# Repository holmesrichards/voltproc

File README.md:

# Voltage processor

This is a voltage processor module based on designs by ARP and MFOS.

There are two sum sections: One has four inputs, two with attenuators (normaled to -10 V and +10 V) and two with fixed unity gain; the other has two inputs, one with attenuator (normaled to +10 V) and one with fixed unity gain. Each sum has two outputs, normal and inverted.

There also is a lag processor section. Switches allow selection of slow or fast ranges and RC or linear ramping, and a knob adjusts the lag time.

The sum sections are derived from the ARP 2600 schematics. Differences:

* Obviously, this is a module, so there is no normal connection to keyboard CV; instead the second input of the first sum is normaled to +10 V.
* Added second inverting stages for normal plus inverted outputs.
* TL07x op amps in place of LM301.
* Added series output resistors.

The lag processor is based on a section of the MFOS Multi Function Module. Differences:

* Common input and output for both linear and RC circuits.
* Shorter minimum linear lag time.
* 1k series resistors on outputs.

## Current draw
20 mA +12 V, 20 mA -12 V

## Photos

## Documentation

* [Schematic](Docs/voltproc.pdf)
* PCB layout: [front](Docs/voltproc_layout_front.pdf), [back](Docs/voltproc_layout_back.pdf)
* [BOM](Docs/voltproc_bom.md)
* [Build notes](Docs/build.md)
* [Blog post](https://analogoutputblog.wordpress.com/2022/11/26/processing-voltages/)

## GitHub repository

* [https://github.com/holmesrichards/voltproc](https://github.com/holmesrichards/voltproc)

## Submodules

## Submodules

This repo uses submodules aoKicad and Kosmo_panel, which provide needed libaries for KiCad. To clone:

```
git clone git@github.com:holmesrichards/voltproc.git
git submodule init
git submodule update
```

Alternatively do

```
git clone --recurse-submodules git@github.com:holmesrichards/voltproc.git
```

Or if you download the repository as a zip file, you must also click on the "aoKicad" and "Kosmo\_panel" links on the GitHub page (they'll have "@ something" after them) and download them as separate zip files which you can unzip into this repo's aoKicad and Kosmo\_panel directories.

If desired, copy the files from aoKicad and Kosmo\_panel to wherever you prefer (your KiCad user library directory, for instance, if you have one). Then in KiCad, go into Edit Symbols and add symbol libraries 

```
aoKicad/ao_symbols
Kosmo_panel/Kosmo
```
and go into Edit Footprints and add footprint libraries 
```
aoKicad/ao_tht
Kosmo_panel/Kosmo_panel.
```

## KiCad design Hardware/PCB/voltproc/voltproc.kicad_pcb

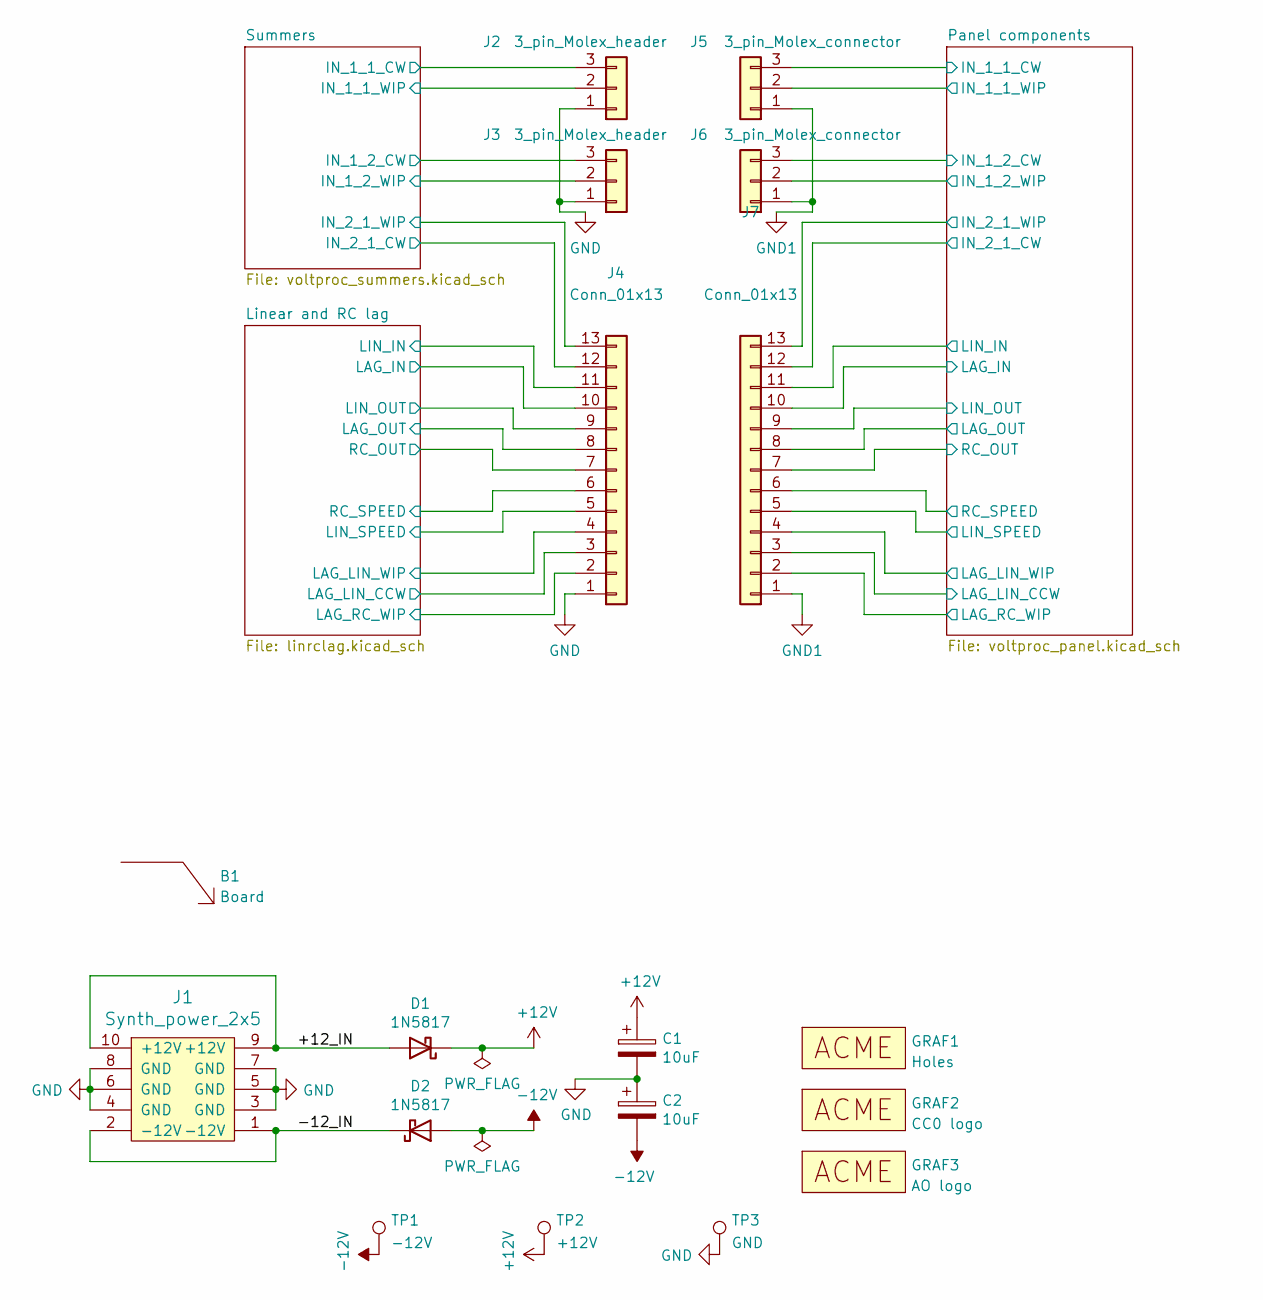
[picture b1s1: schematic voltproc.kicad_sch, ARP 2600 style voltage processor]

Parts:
B1: Board; Board_Marker
C1, C2: 10uF; CP_Radial_D6.3mm_P2.50mm
D1, D2: 1N5817; D_DO-41_SOD81_P10.16mm_Horizontal
GRAF1: Holes; voltproc_panel_holes
GRAF2: CC0 logo; CC0_logo
GRAF3: AO logo; analogoutput
J1: Synth_power_2x5; Power_Header
J2, J3: 3_pin_Molex_header; Molex_KK-254_AE-6410-03A_1x03_P2.54mm_Vertical
J4: Conn_01x13; PinHeader_1x13_P2.54mm_Vertical
J5, J6: 3_pin_Molex_connector; Molex_KK-254_AE-6410-03A_1x03_P2.54mm_Vertical
J7: Conn_01x13; PinSocket_1x13_P2.54mm_Vertical
TP1: -12V; TestPoint_THTPad_D1.5mm_Drill0.7mm
TP2: +12V; TestPoint_THTPad_D1.5mm_Drill0.7mm
TP3: GND; TestPoint_THTPad_D1.5mm_Drill0.7mm

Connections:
+12V: C1.1, D1.1 (K), TP2.1; also elsewhere on the board
-12V: C2.2, D2.2 (A), TP1.1; also elsewhere on the board
/+12_IN: D1.2 (A), J1.9 (+12V), J1.10 (+12V)
/-12_IN: D2.1 (K), J1.1 (-12V), J1.2 (-12V)
/Linear and RC lag/LAG_IN: J4.10; also elsewhere on the board
/Linear and RC lag/LAG_LIN_CCW: J4.3; also elsewhere on the board
/Linear and RC lag/LAG_LIN_WIP: J4.4; also elsewhere on the board
/Linear and RC lag/LAG_OUT: J4.8; also elsewhere on the board
/Linear and RC lag/LAG_RC_WIP: J4.2; also elsewhere on the board
/Linear and RC lag/LIN_IN: J4.11; also elsewhere on the board
/Linear and RC lag/LIN_OUT: J4.9; also elsewhere on the board
/Linear and RC lag/LIN_SPEED: J4.5; also elsewhere on the board
/Linear and RC lag/RC_OUT: J4.7; also elsewhere on the board
/Linear and RC lag/RC_SPEED: J4.6; also elsewhere on the board
/Panel components/IN_2_1_CW: J7.12; also elsewhere on the board
/Panel components/IN_2_1_WIP: J7.13; also elsewhere on the board
/Panel components/LAG_IN: J7.10; also elsewhere on the board
/Panel components/LAG_LIN_CCW: J7.3; also elsewhere on the board
/Panel components/LAG_LIN_WIP: J7.4; also elsewhere on the board
/Panel components/LAG_OUT: J7.8; also elsewhere on the board
/Panel components/LAG_RC_WIP: J7.2; also elsewhere on the board
/Panel components/LIN_IN: J7.11; also elsewhere on the board
/Panel components/LIN_OUT: J7.9; also elsewhere on the board
/Panel components/LIN_SPEED: J7.5; also elsewhere on the board
/Panel components/RC_OUT: J7.7; also elsewhere on the board
/Panel components/RC_SPEED: J7.6; also elsewhere on the board
/Summers/IN_1_1_CW: J2.3; also elsewhere on the board
/Summers/IN_1_1_WIP: J2.2; also elsewhere on the board
/Summers/IN_1_2_CW: J3.3; also elsewhere on the board
/Summers/IN_1_2_WIP: J3.2; also elsewhere on the board
/Summers/IN_2_1_CW: J4.12; also elsewhere on the board
/Summers/IN_2_1_WIP: J4.13; also elsewhere on the board
GND: C1.2, C2.1, J1.3 (GND), J1.4 (GND), J1.5 (GND), J1.6 (GND), J1.7 (GND), J1.8 (GND), J2.1, J3.1, J4.1, TP3.1; also elsewhere on the board
GND1: J5.1, J6.1, J7.1; also elsewhere on the board

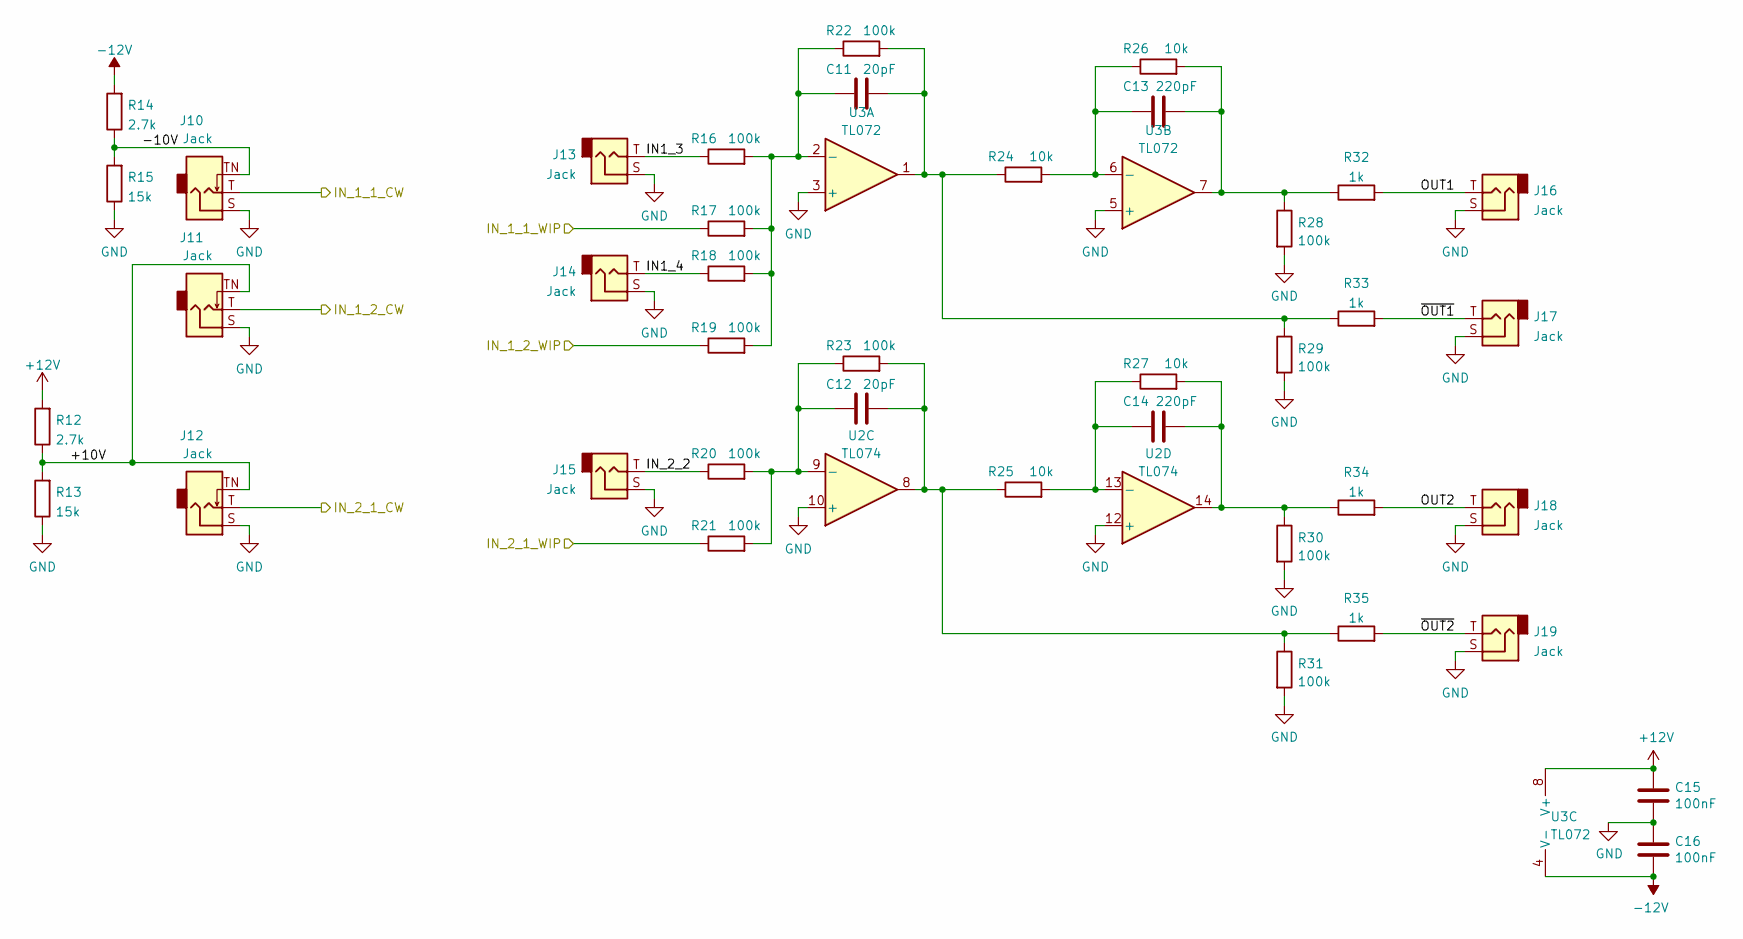
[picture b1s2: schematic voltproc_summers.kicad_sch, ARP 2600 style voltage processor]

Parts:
C11, C12: 20pF; C_Disc_D3.0mm_W1.6mm_P2.50mm
C13, C14: 220pF; C_Disc_D3.0mm_W1.6mm_P2.50mm
C15, C16: 100nF; C_Disc_D3.0mm_W1.6mm_P2.50mm
J10, J11, J12, J13, J14, J15, J16, J17, J18, J19: Jack; Jack_6.35mm_PJ_629HAN_slots
R12, R14: 2.7k; R_Axial_DIN0207_L6.3mm_D2.5mm_P10.16mm_Horizontal
R13, R15: 15k; R_Axial_DIN0207_L6.3mm_D2.5mm_P10.16mm_Horizontal
R16, R17, R18, R19, R20, R21, R22, R23, R28, R29, R30, R31: 100k; R_Axial_DIN0207_L6.3mm_D2.5mm_P10.16mm_Horizontal
R24, R25, R26, R27: 10k; R_Axial_DIN0207_L6.3mm_D2.5mm_P10.16mm_Horizontal
R32, R33, R34, R35: 1k; R_Axial_DIN0207_L6.3mm_D2.5mm_P10.16mm_Horizontal
U2: TL074; DIP-14_W7.62mm_Socket_LongPads
U3: TL072; DIP-8_W7.62mm_Socket_LongPads

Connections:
+12V: C15.1, R12.2, U3.8 (V+); also elsewhere on the board
-12V: C16.2, R14.2, U3.4 (V-); also elsewhere on the board
/Summers/+10V: J11.TN, J12.TN, R12.1, R13.2
/Summers/-10V: J10.TN, R14.1, R15.2
/Summers/IN1_3: J13.T, R16.1
/Summers/IN1_4: J14.T, R18.1
/Summers/IN_1_1_CW: J10.T; also elsewhere on the board
/Summers/IN_1_1_WIP: R17.1; also elsewhere on the board
/Summers/IN_1_2_CW: J11.T; also elsewhere on the board
/Summers/IN_1_2_WIP: R19.1; also elsewhere on the board
/Summers/IN_2_1_CW: J12.T; also elsewhere on the board
/Summers/IN_2_1_WIP: R21.1; also elsewhere on the board
/Summers/IN_2_2: J15.T, R20.1
/Summers/OUT1: J16.T, R32.2
/Summers/OUT2: J18.T, R34.2
/Summers/~OUT1: J17.T, R33.2
/Summers/~OUT2: J19.T, R35.2
GND: C15.2, C16.1, J10.S, J11.S, J12.S, J13.S, J14.S, J15.S, J16.S, J17.S, J18.S, J19.S, R13.1, R15.1, R28.2, R29.2, R30.2, R31.2, U2.10 (+), U2.12 (+), U3.3 (+), U3.5 (+); also elsewhere on the board
unnamed: C11.1, R16.2, R17.2, R18.2, R19.2, R22.1, U3.2 (-)
unnamed: C11.2, R22.2, R24.1, R29.1, R33.1, U3.1
unnamed: C12.1, R20.2, R21.2, R23.1, U2.9 (-)
unnamed: C12.2, R23.2, R25.1, R31.1, R35.1, U2.8
unnamed: C13.1, R24.2, R26.1, U3.6 (-)
unnamed: C13.2, R26.2, R28.1, R32.1, U3.7
unnamed: C14.1, R25.2, R27.1, U2.13 (-)
unnamed: C14.2, R27.2, R30.1, R34.1, U2.14

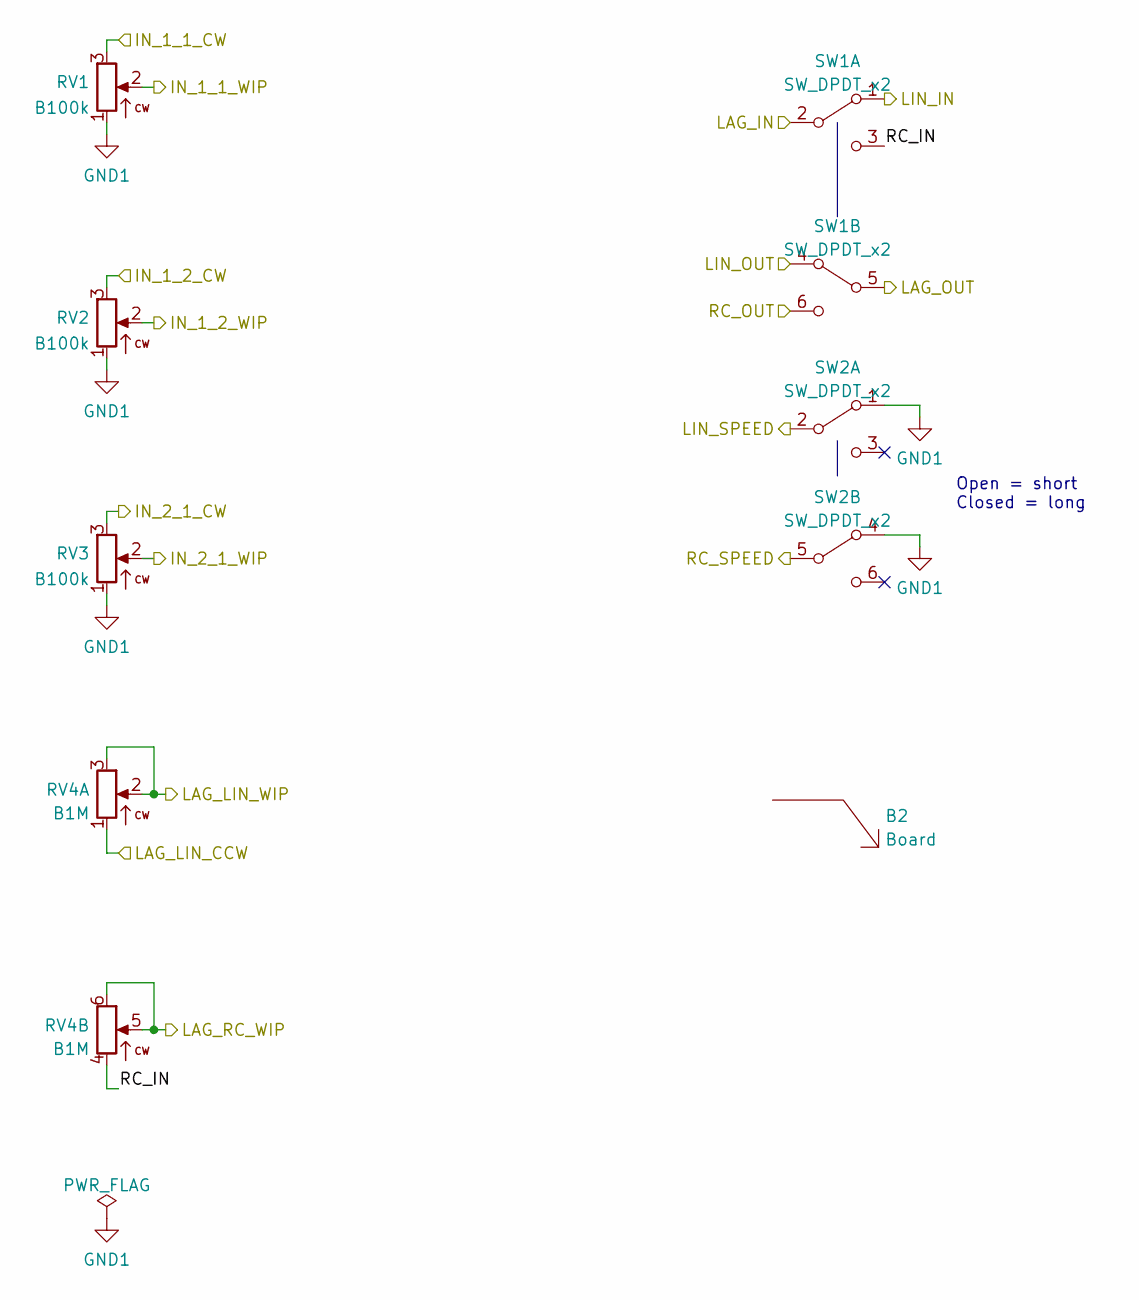
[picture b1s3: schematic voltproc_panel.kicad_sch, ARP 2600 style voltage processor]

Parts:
B2: Board; Board_Marker
RV1, RV2: B100k
RV3: B100k; Potentiometer_Alpha_16mm_Single_Vertical
RV4: B1M; Potentiometer_Alpha_16mm_Dual_Vertical
SW1, SW2: SW_DPDT_x2; DPDT-toggle-switch-1M-seriesx

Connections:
/Panel components/IN_2_1_CW: RV3.3; also elsewhere on the board
/Panel components/IN_2_1_WIP: RV3.2; also elsewhere on the board
/Panel components/LAG_IN: SW1.2 (B); also elsewhere on the board
/Panel components/LAG_LIN_CCW: RV4.1; also elsewhere on the board
/Panel components/LAG_LIN_WIP: RV4.2, RV4.3; also elsewhere on the board
/Panel components/LAG_OUT: SW1.5 (B); also elsewhere on the board
/Panel components/LAG_RC_WIP: RV4.5, RV4.6; also elsewhere on the board
/Panel components/LIN_IN: SW1.1 (A); also elsewhere on the board
/Panel components/LIN_OUT: SW1.4 (A); also elsewhere on the board
/Panel components/LIN_SPEED: SW2.2 (B); also elsewhere on the board
/Panel components/RC_IN: RV4.4, SW1.3 (C)
/Panel components/RC_OUT: SW1.6 (C); also elsewhere on the board
/Panel components/RC_SPEED: SW2.5 (B); also elsewhere on the board
GND1: RV1.1, RV2.1, RV3.1, SW2.1 (A), SW2.4 (A); also elsewhere on the board

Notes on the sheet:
Open = short Closed = long

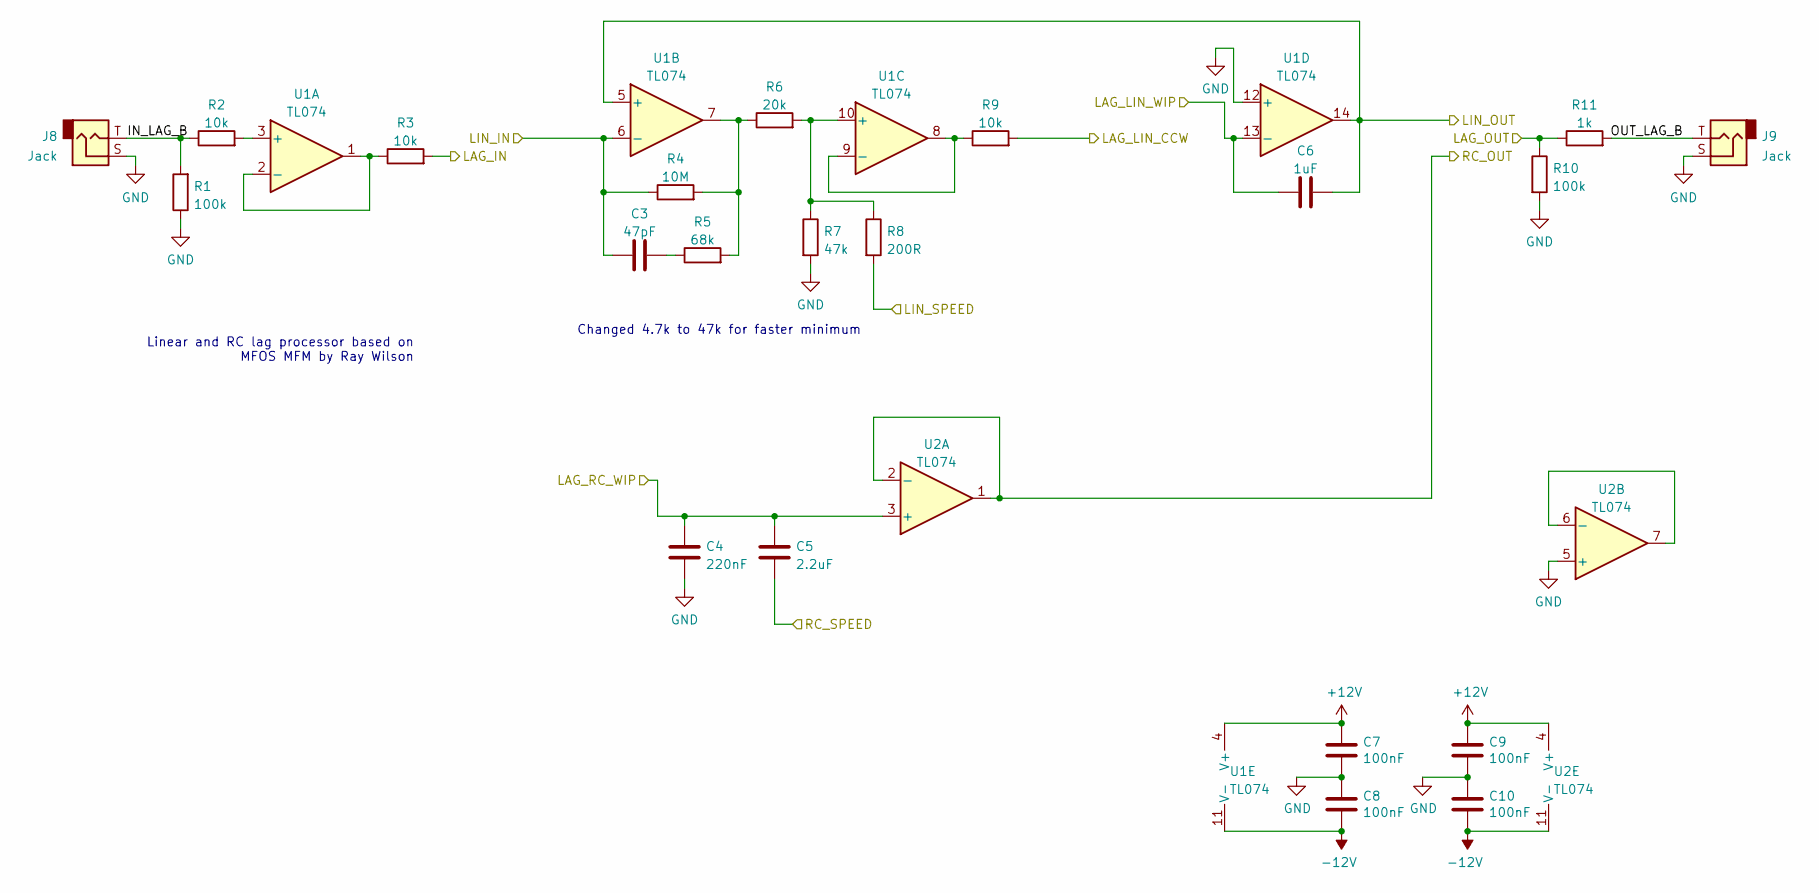
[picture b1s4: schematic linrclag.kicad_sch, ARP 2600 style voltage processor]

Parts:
C3: 47pF; C_Disc_D5.0mm_W2.5mm_P5.00mm
C4: 220nF; C_Rect_L7.2mm_W2.5mm_P5.00mm_FKS2_FKP2_MKS2_MKP2
C5: 2.2uF; C_Radial_D5.0mm_H11.0mm_P2.00mm
C6: 1uF; C_Rect_L7.2mm_W7.2mm_P5.00mm_FKS2_FKP2_MKS2_MKP2
C7, C8, C9, C10: 100nF; C_Disc_D3.0mm_W1.6mm_P2.50mm
J8, J9: Jack; Jack_6.35mm_PJ_629HAN_slots
R1, R10: 100k; R_Axial_DIN0207_L6.3mm_D2.5mm_P10.16mm_Horizontal
R2, R3, R9: 10k; R_Axial_DIN0207_L6.3mm_D2.5mm_P10.16mm_Horizontal
R4: 10M; R_Axial_DIN0207_L6.3mm_D2.5mm_P10.16mm_Horizontal
R5: 68k; R_Axial_DIN0207_L6.3mm_D2.5mm_P10.16mm_Horizontal
R6: 20k; R_Axial_DIN0207_L6.3mm_D2.5mm_P10.16mm_Horizontal
R7: 47k; R_Axial_DIN0207_L6.3mm_D2.5mm_P10.16mm_Horizontal
R8: 200R; R_Axial_DIN0207_L6.3mm_D2.5mm_P10.16mm_Horizontal
R11: 1k; R_Axial_DIN0207_L6.3mm_D2.5mm_P10.16mm_Horizontal
U1, U2: TL074; DIP-14_W7.62mm_Socket_LongPads

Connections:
+12V: C7.1, C9.1, U1.4 (V+), U2.4 (V+); also elsewhere on the board
-12V: C8.2, C10.2, U1.11 (V-), U2.11 (V-); also elsewhere on the board
/Linear and RC lag/IN_LAG_B: J8.T, R1.2, R2.1
/Linear and RC lag/LAG_IN: R3.2; also elsewhere on the board
/Linear and RC lag/LAG_LIN_CCW: R9.2; also elsewhere on the board
/Linear and RC lag/LAG_LIN_WIP: C6.1, U1.13 (-); also elsewhere on the board
/Linear and RC lag/LAG_OUT: R10.1, R11.1; also elsewhere on the board
/Linear and RC lag/LAG_RC_WIP: C4.1, C5.1, U2.3 (+); also elsewhere on the board
/Linear and RC lag/LIN_IN: C3.1, R4.1, U1.6 (-); also elsewhere on the board
/Linear and RC lag/LIN_OUT: C6.2, U1.5 (+), U1.14; also elsewhere on the board
/Linear and RC lag/LIN_SPEED: R8.2; also elsewhere on the board
/Linear and RC lag/OUT_LAG_B: J9.T, R11.2
/Linear and RC lag/RC_OUT: U2.1, U2.2 (-); also elsewhere on the board
/Linear and RC lag/RC_SPEED: C5.2; also elsewhere on the board
GND: C4.2, C7.2, C8.1, C9.2, C10.1, J8.S, J9.S, R1.1, R7.2, R10.2, U1.12 (+), U2.5 (+); also elsewhere on the board
unnamed: C3.2, R5.1
unnamed: R2.2, U1.3 (+)
unnamed: R3.1, U1.1, U1.2 (-)
unnamed: R4.2, R5.2, R6.1, U1.7
unnamed: R6.2, R7.1, R8.1, U1.10 (+)
unnamed: R9.1, U1.8, U1.9 (-)
unnamed: U2.6 (-), U2.7

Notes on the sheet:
Linear and RC lag processor based on MFOS MFM by Ray Wilson
Changed 4.7k to 47k for faster minimum

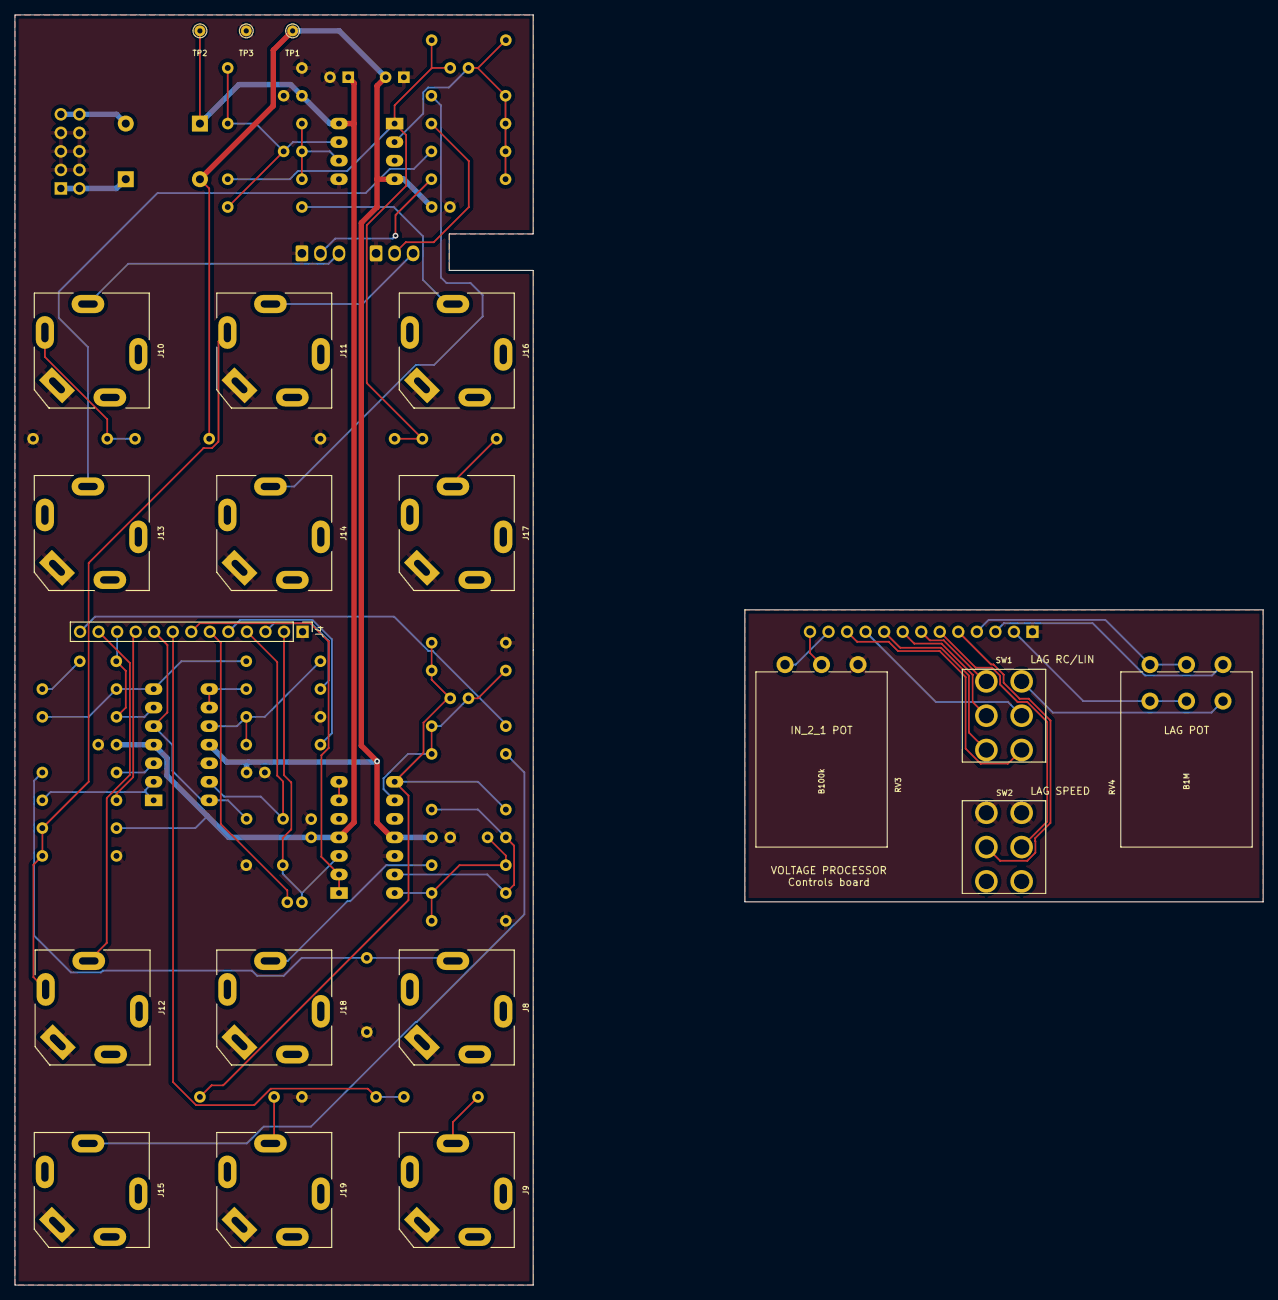
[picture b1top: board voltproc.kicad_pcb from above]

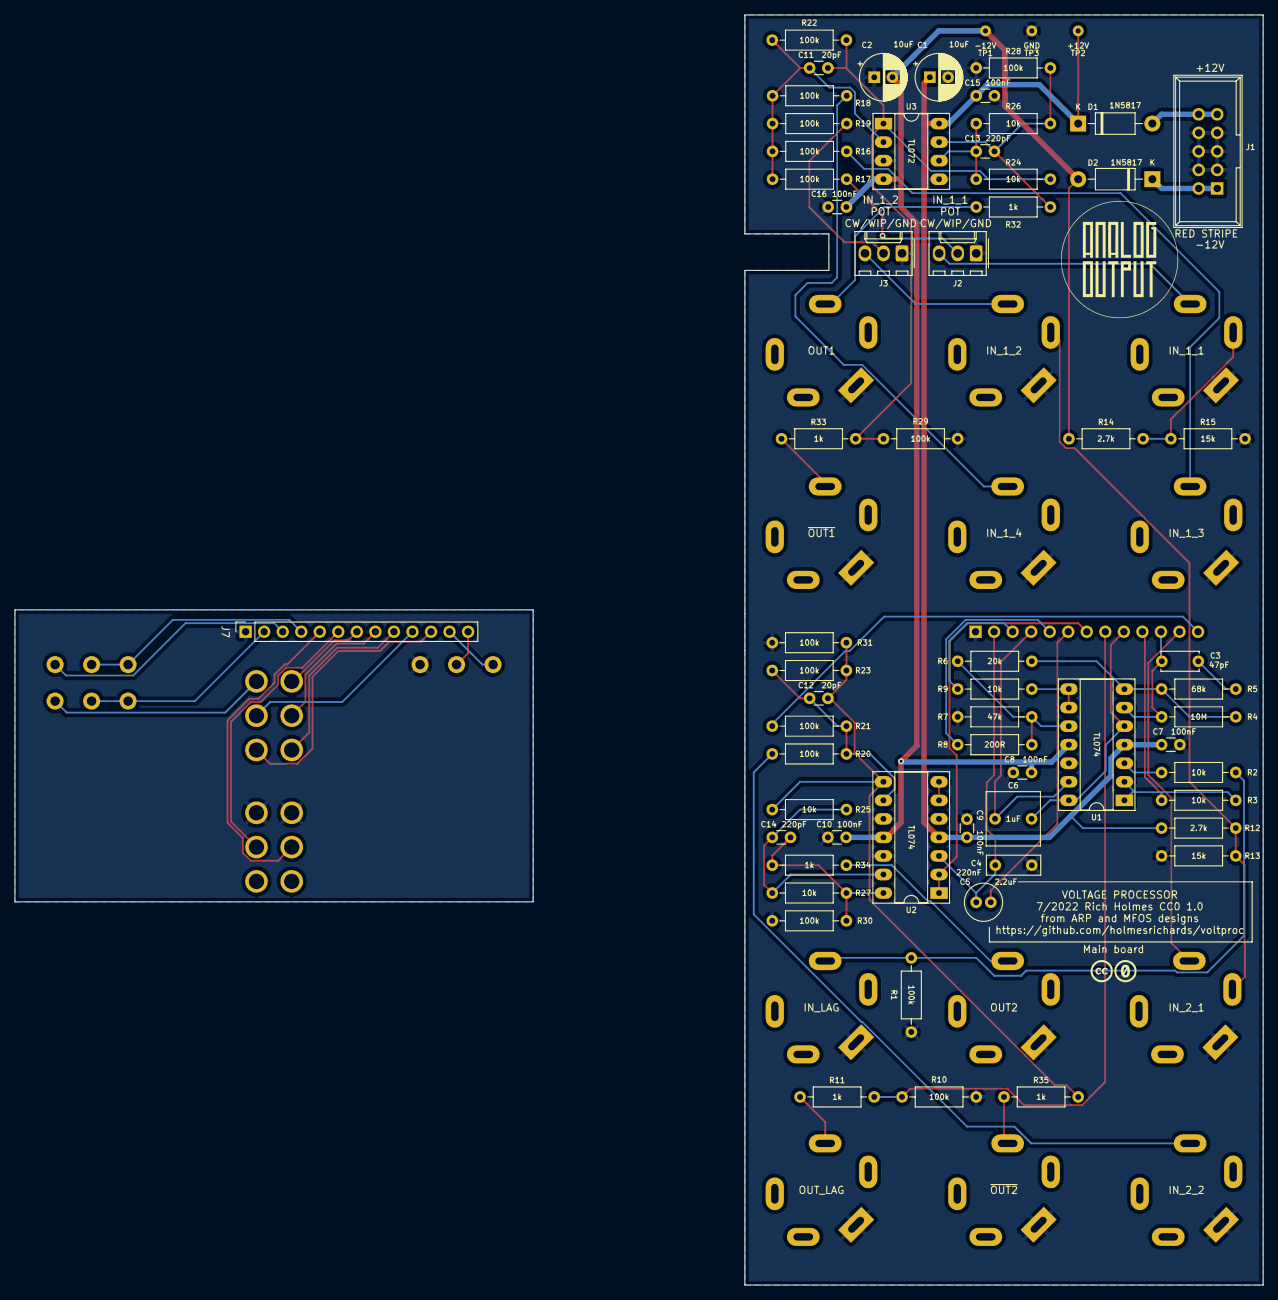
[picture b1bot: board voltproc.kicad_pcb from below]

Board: 2 copper layers, 71.0 x 174.0 mm, 85 parts (62 on the bottom side), 61 nets.

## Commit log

2021-11-23 Initial version
2021-11-24 normal 2nd pot on 1st section
2021-11-25 Update pot symbols
2021-12-05 README edit; panel art
2021-12-25 README
2022-02-01 Better .gitignore; add test points
2022-04-03 reorg schematic, RC and linear lag
2022-04-30 Redo layout
2022-06-10 post breadboard revisions
2022-06-20 Kosmo_panel branch fix
2022-07-08 Tidy up PCB
2022-07-08 Panel KiCad
2022-08-19 CC0 add version
2022-09-23 Pre fab tweaks, Gerbers, cap descriptions
2022-11-09 Fix dual pot footprint
2022-11-12 gerbers
2022-11-12 final pre fab tweaks
2022-11-12 update png
2022-11-26 R7->47k; documentation and photos
2022-11-26 License
2022-11-26 Updated schem
2022-11-26 Typo
2022-11-26 Add blog post link
2022-12-02 Glare at one nonconformist jack and make it behave

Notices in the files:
Hardware/PCB/voltproc/voltproc.kicad_pcb:
7/2022 Rich Holmes CC0 1.0
